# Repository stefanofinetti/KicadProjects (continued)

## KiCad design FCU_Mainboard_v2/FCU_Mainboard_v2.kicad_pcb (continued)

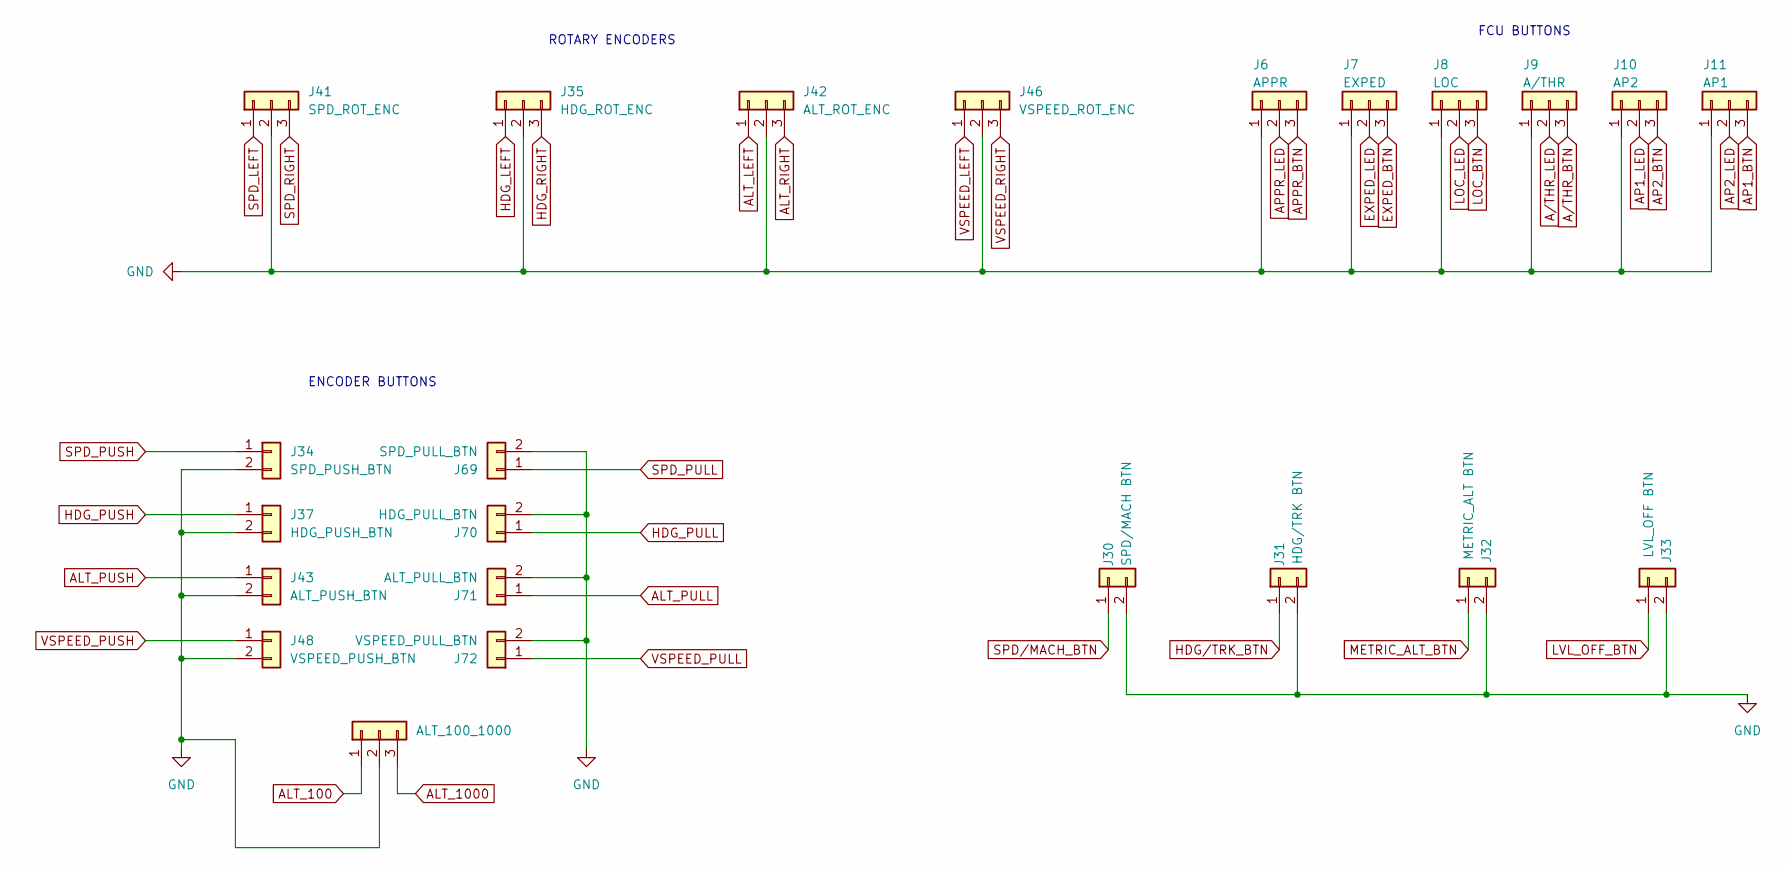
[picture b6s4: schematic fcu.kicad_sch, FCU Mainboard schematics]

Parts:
J6: APPR; JST_EH_B3B-EH-A_1x03_P2.50mm_Vertical
J7: EXPED; JST_EH_B3B-EH-A_1x03_P2.50mm_Vertical
J8: LOC; JST_EH_B3B-EH-A_1x03_P2.50mm_Vertical
J9: A/THR; JST_EH_B3B-EH-A_1x03_P2.50mm_Vertical
J10: AP2; JST_EH_B3B-EH-A_1x03_P2.50mm_Vertical
J11: AP1; JST_EH_B3B-EH-A_1x03_P2.50mm_Vertical
J30: SPD/MACH BTN; JST_EH_B2B-EH-A_1x02_P2.50mm_Vertical
J31: HDG/TRK BTN; JST_EH_B2B-EH-A_1x02_P2.50mm_Vertical
J32: METRIC_ALT BTN; JST_EH_B2B-EH-A_1x02_P2.50mm_Vertical
J33: LVL_OFF BTN; JST_EH_B2B-EH-A_1x02_P2.50mm_Vertical
J34: SPD_PUSH_BTN; JST_EH_B2B-EH-A_1x02_P2.50mm_Vertical
J35: HDG_ROT_ENC; JST_EH_B3B-EH-A_1x03_P2.50mm_Vertical
J37: HDG_PUSH_BTN; JST_EH_B2B-EH-A_1x02_P2.50mm_Vertical
J41: SPD_ROT_ENC; JST_EH_B3B-EH-A_1x03_P2.50mm_Vertical
J42: ALT_ROT_ENC; JST_EH_B3B-EH-A_1x03_P2.50mm_Vertical
J43: ALT_PUSH_BTN; JST_EH_B2B-EH-A_1x02_P2.50mm_Vertical
J45: ALT_100_1000; JST_EH_B3B-EH-A_1x03_P2.50mm_Vertical
J46: VSPEED_ROT_ENC; JST_EH_B3B-EH-A_1x03_P2.50mm_Vertical
J48: VSPEED_PUSH_BTN; JST_EH_B2B-EH-A_1x02_P2.50mm_Vertical
J69: SPD_PULL_BTN; JST_EH_B2B-EH-A_1x02_P2.50mm_Vertical
J70: HDG_PULL_BTN; JST_EH_B2B-EH-A_1x02_P2.50mm_Vertical
J71: ALT_PULL_BTN; JST_EH_B2B-EH-A_1x02_P2.50mm_Vertical
J72: VSPEED_PULL_BTN; JST_EH_B2B-EH-A_1x02_P2.50mm_Vertical

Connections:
ALT_100: J45.1; also elsewhere on the board
ALT_1000: J45.3; also elsewhere on the board
ALT_LEFT: J42.1; also elsewhere on the board
ALT_PULL: J71.1; also elsewhere on the board
ALT_PUSH: J43.1; also elsewhere on the board
ALT_RIGHT: J42.3; also elsewhere on the board
AP1_BTN: J11.3; also elsewhere on the board
AP1_LED: J10.2; also elsewhere on the board
AP2_BTN: J10.3; also elsewhere on the board
AP2_LED: J11.2; also elsewhere on the board
APPR_BTN: J6.3; also elsewhere on the board
APPR_LED: J6.2; also elsewhere on the board
A/THR_BTN: J9.3; also elsewhere on the board
A/THR_LED: J9.2; also elsewhere on the board
EXPED_BTN: J7.3; also elsewhere on the board
EXPED_LED: J7.2; also elsewhere on the board
GND: J6.1, J7.1, J8.1, J9.1, J10.1, J11.1, J30.2, J31.2, J32.2, J33.2, J34.2, J35.2, J37.2, J41.2, J42.2, J43.2, J45.2, J46.2, J48.2, J69.2, J70.2, J71.2, J72.2; also elsewhere on the board
HDG_LEFT: J35.1; also elsewhere on the board
HDG_PULL: J70.1; also elsewhere on the board
HDG_PUSH: J37.1; also elsewhere on the board
HDG_RIGHT: J35.3; also elsewhere on the board
HDG/TRK_BTN: J31.1; also elsewhere on the board
LOC_BTN: J8.3; also elsewhere on the board
LOC_LED: J8.2; also elsewhere on the board
LVL_OFF_BTN: J33.1; also elsewhere on the board
METRIC_ALT_BTN: J32.1; also elsewhere on the board
SPD_LEFT: J41.1; also elsewhere on the board
SPD_PULL: J69.1; also elsewhere on the board
SPD_PUSH: J34.1; also elsewhere on the board
SPD_RIGHT: J41.3; also elsewhere on the board
SPD/MACH_BTN: J30.1; also elsewhere on the board
VSPEED_LEFT: J46.1; also elsewhere on the board
VSPEED_PULL: J72.1; also elsewhere on the board
VSPEED_PUSH: J48.1; also elsewhere on the board
VSPEED_RIGHT: J46.3; also elsewhere on the board

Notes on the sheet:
ROTARY ENCODERS
ENCODER BUTTONS
FCU BUTTONS

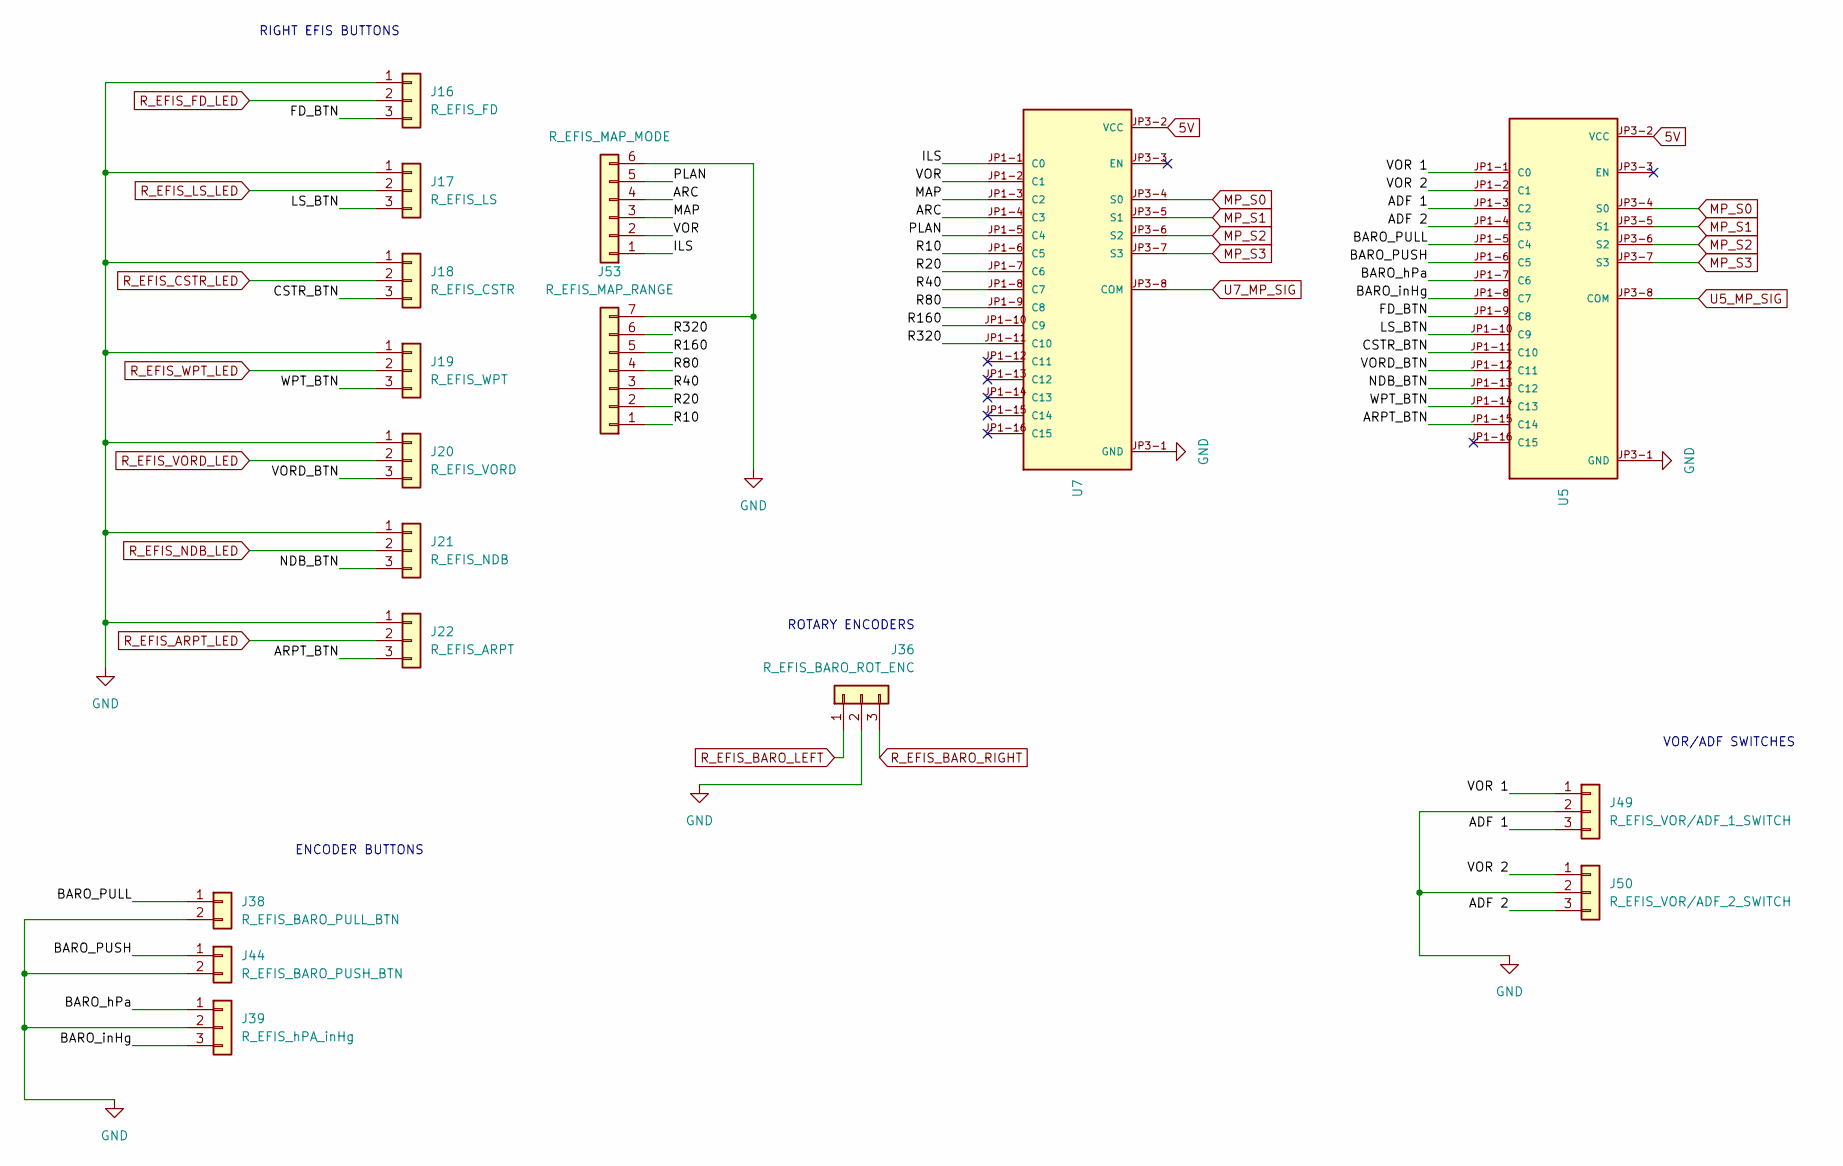
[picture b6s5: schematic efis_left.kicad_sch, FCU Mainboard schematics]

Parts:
J16: R_EFIS_FD; JST_EH_B3B-EH-A_1x03_P2.50mm_Vertical
J17: R_EFIS_LS; JST_EH_B3B-EH-A_1x03_P2.50mm_Vertical
J18: R_EFIS_CSTR; JST_EH_B3B-EH-A_1x03_P2.50mm_Vertical
J19: R_EFIS_WPT; JST_EH_B3B-EH-A_1x03_P2.50mm_Vertical
J20: R_EFIS_VORD; JST_EH_B3B-EH-A_1x03_P2.50mm_Vertical
J21: R_EFIS_NDB; JST_EH_B3B-EH-A_1x03_P2.50mm_Vertical
J22: R_EFIS_ARPT; JST_EH_B3B-EH-A_1x03_P2.50mm_Vertical
J36: R_EFIS_BARO_ROT_ENC; JST_EH_B3B-EH-A_1x03_P2.50mm_Vertical
J38: R_EFIS_BARO_PULL_BTN; JST_EH_B2B-EH-A_1x02_P2.50mm_Vertical
J39: R_EFIS_hPA_inHg; JST_EH_B3B-EH-A_1x03_P2.50mm_Vertical
J44: R_EFIS_BARO_PUSH_BTN; JST_EH_B2B-EH-A_1x02_P2.50mm_Vertical
J49: R_EFIS_VOR/ADF_1_SWITCH; JST_EH_B3B-EH-A_1x03_P2.50mm_Vertical
J50: R_EFIS_VOR/ADF_2_SWITCH; JST_EH_B3B-EH-A_1x03_P2.50mm_Vertical
J51: R_EFIS_MAP_MODE; JST_EH_B6B-EH-A_1x06_P2.50mm_Vertical
J53: R_EFIS_MAP_RANGE; JST_EH_B7B-EH-A_1x07_P2.50mm_Vertical
U5, U7: Multiplexer CD74HC4067 Breakout; MODULE_BOB-09056; PARTREV v11

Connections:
5V: U5.JP3-2 (VCC), U7.JP3-2 (VCC); also elsewhere on the board
/EFIS_LEFT/ADF 1: J49.3, U5.JP1-3 (C2)
/EFIS_LEFT/ADF 2: J50.3, U5.JP1-4 (C3)
/EFIS_LEFT/ARC: J51.4, U7.JP1-4 (C3)
/EFIS_LEFT/ARPT_BTN: J22.3, U5.JP1-15 (C14)
/EFIS_LEFT/BARO_PULL: J38.1, U5.JP1-5 (C4)
/EFIS_LEFT/BARO_PUSH: J44.1, U5.JP1-6 (C5)
/EFIS_LEFT/BARO_hPa: J39.1, U5.JP1-7 (C6)
/EFIS_LEFT/BARO_inHg: J39.3, U5.JP1-8 (C7)
/EFIS_LEFT/CSTR_BTN: J18.3, U5.JP1-11 (C10)
/EFIS_LEFT/FD_BTN: J16.3, U5.JP1-9 (C8)
/EFIS_LEFT/ILS: J51.1, U7.JP1-1 (C0)
/EFIS_LEFT/LS_BTN: J17.3, U5.JP1-10 (C9)
/EFIS_LEFT/MAP: J51.3, U7.JP1-3 (C2)
/EFIS_LEFT/NDB_BTN: J21.3, U5.JP1-13 (C12)
/EFIS_LEFT/PLAN: J51.5, U7.JP1-5 (C4)
/EFIS_LEFT/R10: J53.1, U7.JP1-6 (C5)
/EFIS_LEFT/R20: J53.2, U7.JP1-7 (C6)
/EFIS_LEFT/R40: J53.3, U7.JP1-8 (C7)
/EFIS_LEFT/R80: J53.4, U7.JP1-9 (C8)
/EFIS_LEFT/R160: J53.5, U7.JP1-10 (C9)
/EFIS_LEFT/R320: J53.6, U7.JP1-11 (C10)
/EFIS_LEFT/VOR: J51.2, U7.JP1-2 (C1)
/EFIS_LEFT/VOR 1: J49.1, U5.JP1-1 (C0)
/EFIS_LEFT/VOR 2: J50.1, U5.JP1-2 (C1)
/EFIS_LEFT/VORD_BTN: J20.3, U5.JP1-12 (C11)
/EFIS_LEFT/WPT_BTN: J19.3, U5.JP1-14 (C13)
GND: J16.1, J17.1, J18.1, J19.1, J20.1, J21.1, J22.1, J36.2, J38.2, J39.2, J44.2, J49.2, J50.2, J51.6, J53.7, U5.JP3-1 (GND), U7.JP3-1 (GND); also elsewhere on the board
MP_S0: U5.JP3-4 (S0), U7.JP3-4 (S0); also elsewhere on the board
MP_S1: U5.JP3-5 (S1), U7.JP3-5 (S1); also elsewhere on the board
MP_S2: U5.JP3-6 (S2), U7.JP3-6 (S2); also elsewhere on the board
MP_S3: U5.JP3-7 (S3), U7.JP3-7 (S3); also elsewhere on the board
R_EFIS_ARPT_LED: J22.2; also elsewhere on the board
R_EFIS_BARO_LEFT: J36.1; also elsewhere on the board
R_EFIS_BARO_RIGHT: J36.3; also elsewhere on the board
R_EFIS_CSTR_LED: J18.2; also elsewhere on the board
R_EFIS_FD_LED: J16.2; also elsewhere on the board
R_EFIS_LS_LED: J17.2; also elsewhere on the board
R_EFIS_NDB_LED: J21.2; also elsewhere on the board
R_EFIS_VORD_LED: J20.2; also elsewhere on the board
R_EFIS_WPT_LED: J19.2; also elsewhere on the board
U5_MP_SIG: U5.JP3-8 (COM); also elsewhere on the board
U7_MP_SIG: U7.JP3-8 (COM); also elsewhere on the board

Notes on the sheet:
ENCODER BUTTONS
RIGHT EFIS BUTTONS
VOR/ADF SWITCHES
ROTARY ENCODERS

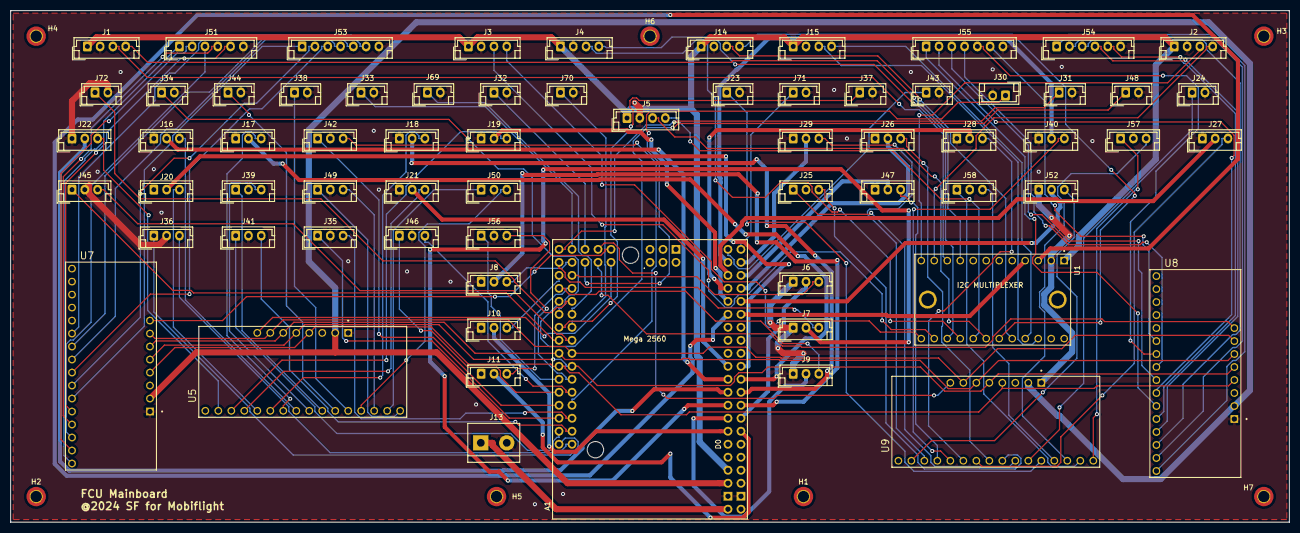
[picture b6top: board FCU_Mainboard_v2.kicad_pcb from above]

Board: 2 copper layers, 250.0 x 100.0 mm, 74 parts (0 on the bottom side), 132 nets.

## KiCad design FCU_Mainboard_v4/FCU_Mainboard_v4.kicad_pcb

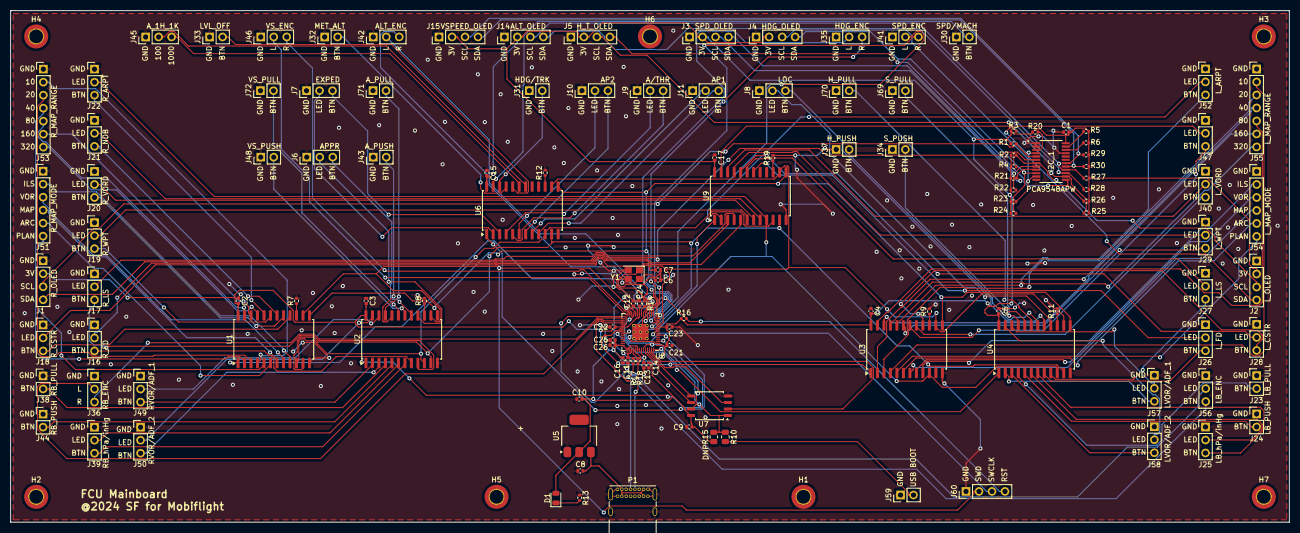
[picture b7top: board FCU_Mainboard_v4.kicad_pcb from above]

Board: 2 copper layers, 250.0 x 100.0 mm, 135 parts (0 on the bottom side), 159 nets.

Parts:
C1, C2, C3, C4, C5, C9, C12, C13, C14, C15, C17, C21, C22, C23, C24, C25, C26: 100nF; Perfect_0402
C6, C7: 15pF; Perfect_0402
C8, C10: 10uF; Perfect_0402
C11, C16: 1uF; Perfect_0402
D1: LED; LED_0805_2012Metric
H1, H2, H3, H4, H5, H6, H7: MountingHole; MountingHole_2.7mm_M2.5_DIN965_Pad_TopBottom
I2C_1: PCA9548APW; SOP65P640X120-24N
J1: R_OLED; PinHeader_1x04_P2.54mm_Vertical
J2: L_OLED; PinHeader_1x04_P2.54mm_Vertical
J3: SPD_OLED; PinHeader_1x04_P2.54mm_Vertical
J4: HDG_OLED; PinHeader_1x04_P2.54mm_Vertical
J5: H_T_OLED; PinHeader_1x04_P2.54mm_Vertical
J6: APPR; PinHeader_1x03_P2.54mm_Vertical
J7: EXPED; PinHeader_1x03_P2.54mm_Vertical
J8: LOC; PinHeader_1x03_P2.54mm_Vertical
J9: A/THR; PinHeader_1x03_P2.54mm_Vertical
J10: AP2; PinHeader_1x03_P2.54mm_Vertical
J11: AP1; PinHeader_1x03_P2.54mm_Vertical
J14: ALT_OLED; PinHeader_1x04_P2.54mm_Vertical
J15: VSPEED_OLED; PinHeader_1x04_P2.54mm_Vertical
J16: R_FD; PinHeader_1x03_P2.54mm_Vertical
J17: R_LS; PinHeader_1x03_P2.54mm_Vertical
J18: R_CSTR; PinHeader_1x03_P2.54mm_Vertical
J19: R_WPT; PinHeader_1x03_P2.54mm_Vertical
J20: R_VORD; PinHeader_1x03_P2.54mm_Vertical
J21: R_NDB; PinHeader_1x03_P2.54mm_Vertical
J22: R_ARPT; PinHeader_1x03_P2.54mm_Vertical
J23: LB_PULL; PinHeader_1x02_P2.54mm_Vertical
J24: LB_PUSH; PinHeader_1x02_P2.54mm_Vertical
J25: LB_hPa/inHg; PinHeader_1x03_P2.54mm_Vertical
J26: L_FD; PinHeader_1x03_P2.54mm_Vertical
J27: L_LS; PinHeader_1x03_P2.54mm_Vertical
J28: L_CSTR; PinHeader_1x03_P2.54mm_Vertical
J29: L_WPT; PinHeader_1x03_P2.54mm_Vertical
J30: SPD/MACH; PinHeader_1x02_P2.54mm_Vertical
J31: HDG/TRK; PinHeader_1x02_P2.54mm_Vertical
J32: MET_ALT; PinHeader_1x02_P2.54mm_Vertical
J33: LVL_OFF; PinHeader_1x02_P2.54mm_Vertical
J34: S_PUSH; PinHeader_1x02_P2.54mm_Vertical
J35: HDG_ENC; PinHeader_1x03_P2.54mm_Vertical
J36: RB_ENC; PinHeader_1x03_P2.54mm_Vertical
J37: H_PUSH; PinHeader_1x02_P2.54mm_Vertical
J38: RB_PULL; PinHeader_1x02_P2.54mm_Vertical
J39: RB_hPa/inHg; PinHeader_1x03_P2.54mm_Vertical
J40: L_VORD; PinHeader_1x03_P2.54mm_Vertical
J41: SPD_ENC; PinHeader_1x03_P2.54mm_Vertical
J42: ALT_ENC; PinHeader_1x03_P2.54mm_Vertical
J43: A_PUSH; PinHeader_1x02_P2.54mm_Vertical
J44: RB_PUSH; PinHeader_1x02_P2.54mm_Vertical
J45: A_1H_1K; PinHeader_1x03_P2.54mm_Vertical
J46: VS_ENC; PinHeader_1x03_P2.54mm_Vertical
J47: L_NDB; PinHeader_1x03_P2.54mm_Vertical
J48: VS_PUSH; PinHeader_1x02_P2.54mm_Vertical
J49: RVOR/ADF_1; PinHeader_1x03_P2.54mm_Vertical
J50: RVOR/ADF_2; PinHeader_1x03_P2.54mm_Vertical
J51: R_MAP_MODE; PinHeader_1x06_P2.54mm_Vertical
J52: L_ARPT; PinHeader_1x03_P2.54mm_Vertical
J53: R_MAP_RANGE; PinHeader_1x07_P2.54mm_Vertical
J54: L_MAP_MODE; PinHeader_1x06_P2.54mm_Vertical
J55: L_MAP_RANGE; PinHeader_1x07_P2.54mm_Vertical
J56: LB_ENC; PinHeader_1x03_P2.54mm_Vertical
J57: LVOR/ADF_1; PinHeader_1x03_P2.54mm_Vertical
J58: LVOR/ADF_2; PinHeader_1x03_P2.54mm_Vertical
J59: Conn_01x02; PinHeader_1x02_P2.54mm_Vertical
J60: RP2040_SWD; PinHeader_1x04_P2.54mm_Vertical
J69: S_PULL; PinHeader_1x02_P2.54mm_Vertical
J70: H_PULL; PinHeader_1x02_P2.54mm_Vertical
J71: A_PULL; PinHeader_1x02_P2.54mm_Vertical
J72: VS_PULL; PinHeader_1x02_P2.54mm_Vertical
P1: USB_C_Plug_USB2.0; USB_C_Receptacle_GCT_USB4085
R1, R2, R3, R4, R5, R6, R21, R22, R23, R24, R25, R26, R27, R28, R29, R30: R4.7K; R_0402_1005Metric
R7, R8, R9, R11, R12, R19, R20: R10K; R_0402_1005Metric
R10: 1k; R_0805_2012Metric
R13: R220; R_0402_1005Metric
R14: 1k; R_0402_1005Metric
R15: DNP; R_0805_2012Metric
R16: 10k; R_0402_1005Metric
R17, R18: 27.4; R_0402_1005Metric
U1, U2, U3, U4, U6, U9: CD74HC4067M; SOIC-24W_7.5x15.4mm_P1.27mm
U5: NCP1117-3.3_SOT223; SOT-223
U7: W25Q128JVS; SOIC-8_5.23x5.23mm_P1.27mm
U8: RP2040; QFN-56-1EP_7x7mm_P0.4mm_EP3.2x3.2mm
Y1: X322512MSB4SI; Crystal_SMD_3225-4Pin_3.2x2.5mm

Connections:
+1V1: C11.1, C12.1, C13.1, U8.23 (DVDD), U8.45 (VREG_VOUT), U8.50 (DVDD)
+3V3: C1.1, C2.1, C3.1, C4.1, C5.1, C9.1, C10.1, C14.1, C15.1, C16.1, C17.1, C21.1, C22.1, C23.1, C24.1, C25.1, C26.1, D1.2 (A), I2C_1.24 (VCC), J1.2, J2.2, J3.2, J4.2, J5.2, J14.2, J15.2, R1.1, R2.2, R3.1, R4.1, R5.2, R6.1, R15.1, R16.1, R20.1, R21.1, R22.1, R23.1, R24.1, R25.1, R26.1, R27.1, R28.1, R29.1, R30.1, U1.24 (VCC), U2.24 (VCC), U3.24 (VCC), U4.24 (VCC), U5.2 (VO), U6.24 (VCC), U7.8 (VCC), U8.1 (IOVDD), U8.10 (IOVDD), U8.22 (IOVDD), U8.33 (IOVDD), U8.42 (IOVDD), U8.43 (ADC_AVDD), U8.44 (VREG_IN), U8.48 (USB_VDD), U8.49 (IOVDD), U9.24 (VCC)
+5V: C8.1, P1.A4 (VBUS), P1.A9 (VBUS), P1.B4 (VBUS), P1.B9 (VBUS), U5.3 (VI)
/OLEDs/ALT_SCL: I2C_1.16 (SC5), J14.3, R27.2
/OLEDs/ALT_SDA: I2C_1.15 (SD5), J14.4, R28.2
/OLEDs/HDG_SCL: I2C_1.11 (SC3), J4.3, R23.2
/OLEDs/HDG_SDA: I2C_1.10 (SD3), J4.4, R24.2
/OLEDs/HDG/TRK_SCL: I2C_1.14 (SC4), J5.3, R25.2
/OLEDs/HDG/TRK_SDA: I2C_1.13 (SD4), J5.4, R26.2
/OLEDs/L_EFIS_SCL: I2C_1.7 (SC1), J2.3, R1.2
/OLEDs/L_EFIS_SDA: I2C_1.4 (SD0), J2.4, R3.2
/OLEDs/R_EFIS_SCL: I2C_1.5 (SC0), J1.3, R2.1
/OLEDs/R_EFIS_SDA: I2C_1.6 (SD1), J1.4, R4.2
/OLEDs/SPD_SCL: I2C_1.9 (SC2), J3.3, R21.2
/OLEDs/SPD_SDA: I2C_1.8 (SD2), J3.4, R22.2
/OLEDs/VSPEED_SCL: I2C_1.18 (SC6), J15.3, R29.2
/OLEDs/VSPEED_SDA: I2C_1.17 (SD6), J15.4, R30.2
/QSPI_SCLK: U7.6 (CLK), U8.52 (QSPI_SCLK)
/QSPI_SD0: U7.5 (DI(IO0)), U8.53 (QSPI_SD0)
/QSPI_SD1: U7.2 (DO(IO1)), U8.55 (QSPI_SD1)
/QSPI_SD2: U7.3 (IO2), U8.54 (QSPI_SD2)
/QSPI_SD3: U7.7 (IO3), U8.51 (QSPI_SD3)
/QSPI_SS: R10.1, R15.2, U7.1 (~CS), U8.56 (QSPI_SS)
/SWCLK: J60.3, U8.25 (SWD)
/SWD: J60.2, U8.24 (SWCLK)
/USB_D+: P1.A6 (D+), R17.1
/USB_D-: P1.A7 (D-), R18.1
/XIN: C6.1, U8.20 (XIN), Y1.3
/XOUT: R14.1, U8.21 (XOUT)
/~RST: J60.4, R16.2, U8.26 (RUN)
/~USB_BOOT: J59.2, R10.2
ALT_100: J45.2, U6.18 (I13)
ALT_1000: J45.3, U6.19 (I12)
ALT_LEFT: J42.2, U8.18 (GPIO15)
ALT_PULL: J71.2, U2.21 (I10)
ALT_PUSH: J43.2, U2.20 (I11)
ALT_RIGHT: J42.3, U8.17 (GPIO14)
AP1_BTN: J11.3, U6.9 (I0)
AP1_LED: J11.2, U6.8 (I1)
AP2_BTN: J10.3, U6.7 (I2)
AP2_LED: J10.2, U6.6 (I3)
APPR_BTN: J6.3, U2.17 (I14)
APPR_LED: J6.2, U2.16 (I15)
A/THR_BTN: J9.3, U6.5 (I4)
A/THR_LED: J9.2, U6.4 (I5)
EXPED_BTN: J7.3, U6.3 (I6)
EXPED_LED: J7.2, U6.2 (I7)
GND: C1.2, C2.2, C3.2, C4.2, C5.2, C6.2, C7.2, C8.2, C9.2, C10.2, C11.2, C12.2, C13.2, C14.2, C15.2, C16.2, C17.2, C21.2, C22.2, C23.2, C24.2, C25.2, C26.2, I2C_1.1 (A0), I2C_1.2 (A1), I2C_1.12 (GND), I2C_1.21 (A2), J1.1, J2.1, J3.1, J4.1, J5.1, J6.1, J7.1, J8.1, J9.1, J10.1, J11.1, J14.1, J15.1, J16.1, J17.1, J18.1, J19.1, J20.1, J21.1, J22.1, J23.1, J24.1, J25.1, J26.1, J27.1, J28.1, J29.1, J30.1, J31.1, J32.1, J33.1, J34.1, J35.1, J36.1, J37.1, J38.1, J39.1, J40.1, J41.1, J42.1, J43.1, J44.1, J45.1, J46.1, J47.1, J48.1, J49.1, J50.1, J51.1, J52.1, J53.1, J54.1, J55.1, J56.1, J57.1, J58.1, J59.1, J60.1, J69.1, J70.1, J71.1, J72.1, P1.A1 (GND), P1.A12 (GND), P1.B1 (GND), P1.B12 (GND), P1.S1 (SHIELD), R7.2, R8.2, R9.2, R11.2, R12.2, R13.1, R19.2, U1.12 (GND), U2.12 (GND), U3.12 (GND), U4.12 (GND), U5.1 (GND), U6.12 (GND), U7.4 (GND), U8.19 (TESTEN), U8.57 (GND), U9.12 (GND), Y1.2, Y1.4
HDG_LEFT: J35.2, U8.16 (GPIO13)
HDG_PULL: J70.2, U4.19 (I12)
HDG_PUSH: J37.2, U4.18 (I13)
HDG_RIGHT: J35.3, U8.15 (GPIO12)
HDG/TRK_BTN: J31.2, U6.22 (I9)
LOC_BTN: J8.3, U4.17 (I14)
LOC_LED: J8.2, U4.16 (I15)
LVL_OFF_BTN: J33.2, U6.20 (I11)
L_ADF_1: J57.3, U4.2 (I7)
L_ADF_2: J58.3, U4.3 (I6)
L_ARC: J54.5, U3.6 (I3)
L_ARPT_BTN: J52.3, U3.20 (I11)
L_BARO_PULL: J23.2, U4.4 (I5)
L_BARO_PUSH: J24.2, U4.5 (I4)
L_BARO_hPa: J25.2, U4.6 (I3)
L_BARO_inHg: J25.3, U4.7 (I2)
L_CSTR_BTN: J28.3, U3.16 (I15)
L_EFIS_ARPT_LED: J52.2, U9.2 (I7)
L_EFIS_BARO_LEFT: J56.2, U8.32 (GPIO21)
L_EFIS_BARO_RIGHT: J56.3, U8.31 (GPIO20)
L_EFIS_CSTR_LED: J28.2, U9.20 (I11)
L_EFIS_FD_LED: J26.2, U9.18 (I13)
L_EFIS_LS_LED: J27.2, U9.19 (I12)
L_EFIS_NDB_LED: J47.2, U9.23 (I8)
L_EFIS_VORD_LED: J40.2, U9.22 (I9)
L_EFIS_WPT_LED: J29.2, U9.21 (I10)
L_FD_BTN: J26.3, U4.8 (I1)
L_ILS: J54.2, U3.9 (I0)
L_LS_BTN: J27.3, U4.9 (I0)
L_MAP: J54.4, U3.7 (I2)
L_NDB_BTN: J47.3, U3.18 (I13)
L_PLAN: J54.6, U3.5 (I4)
L_R10: J55.2, U3.4 (I5)
L_R20: J55.3, U3.3 (I6)
L_R40: J55.4, U3.2 (I7)
L_R80: J55.5, U3.23 (I8)
L_R160: J55.6, U3.22 (I9)
L_R320: J55.7, U3.21 (I10)
L_VOR: J54.3, U3.8 (I1)
L_VORD_BTN: J40.3, U3.17 (I14)
L_VOR_1: J57.2, U4.22 (I9)
L_VOR_2: J58.2, U4.23 (I8)
L_WPT_BTN: J29.3, U3.19 (I12)
METRIC_ALT_BTN: J32.2, U6.21 (I10)
MP_S0: U1.10 (S0), U2.10 (S0), U3.10 (S0), U4.10 (S0), U6.10 (S0), U8.8 (GPIO6), U9.10 (S0)
MP_S1: U1.11 (S1), U2.11 (S1), U3.11 (S1), U4.11 (S1), U6.11 (S1), U8.9 (GPIO7), U9.11 (S1)
MP_S2: U1.14 (S2), U2.14 (S2), U3.14 (S2), U4.14 (S2), U6.14 (S2), U8.11 (GPIO8), U9.14 (S2)
MP_S3: U1.13 (S3), U2.13 (S3), U3.13 (S3), U4.13 (S3), U6.13 (S3), U8.12 (GPIO9), U9.13 (S3)
unnamed: C7.1, R14.2, Y1.1
unnamed: D1.1 (K), R13.2
unnamed: I2C_1.3 (~RESET), R20.2
unnamed: R7.1, U1.15 (~E)
unnamed: R8.1, U2.15 (~E)
unnamed: R9.1, U3.15 (~E)
unnamed: R11.1, U4.15 (~E)
unnamed: R12.1, U6.15 (~E)
unnamed: R18.2, U8.46 (USB_DM)
unnamed: R17.2, U8.47 (USB_DP)
unnamed: R19.1, U9.15 (~E)
R_ADF_1: J49.3, U2.2 (I7)
R_ADF_2: J50.3, U2.3 (I6)
R_ARC: J51.5, U1.6 (I3)
R_ARPT_BTN: J22.3, U1.20 (I11)
R_BARO_PULL: J38.2, U2.4 (I5)
R_BARO_PUSH: J44.2, U2.5 (I4)
R_BARO_hPa: J39.2, U2.6 (I3)
R_BARO_inHg: J39.3, U2.7 (I2)
R_CSTR_BTN: J18.3, U1.16 (I15)
R_EFIS_ARPT_LED: J22.2, U9.9 (I0)
R_EFIS_BARO_LEFT: J36.2, U8.30 (GPIO19)
R_EFIS_BARO_RIGHT: J36.3, U8.29 (GPIO18)
R_EFIS_CSTR_LED: J18.2, U9.5 (I4)
R_EFIS_FD_LED: J16.2, U9.3 (I6)
R_EFIS_LS_LED: J17.2, U9.4 (I5)
R_EFIS_NDB_LED: J21.2, U9.8 (I1)
R_EFIS_VORD_LED: J20.2, U9.7 (I2)
R_EFIS_WPT_LED: J19.2, U9.6 (I3)
R_FD_BTN: J16.3, U2.8 (I1)
R_ILS: J51.2, U1.9 (I0)
R_LS_BTN: J17.3, U2.9 (I0)
R_MAP: J51.4, U1.7 (I2)
R_NDB_BTN: J21.3, U1.18 (I13)
R_PLAN: J51.6, U1.5 (I4)
R_R10: J53.2, U1.4 (I5)
R_R20: J53.3, U1.3 (I6)
R_R40: J53.4, U1.2 (I7)
R_R80: J53.5, U1.23 (I8)
R_R160: J53.6, U1.22 (I9)
R_R320: J53.7, U1.21 (I10)
R_VOR: J51.3, U1.8 (I1)
R_VORD_BTN: J20.3, U1.17 (I14)
R_VOR_1: J49.2, U2.22 (I9)
R_VOR_2: J50.2, U2.23 (I8)
R_WPT_BTN: J19.3, U1.19 (I12)
SCL: I2C_1.22 (SCL), R5.1
SDA: I2C_1.23 (SDA), R6.2
SPD_LEFT: J41.2, U8.14 (GPIO11)
SPD_PULL: J69.2, U4.21 (I10)
SPD_PUSH: J34.2, U4.20 (I11)
SPD_RIGHT: J41.3, U8.13 (GPIO10)
SPD/MACH_BTN: J30.2, U6.23 (I8)
U1_MP_SIG: U1.1 (COM), U8.2 (GPIO0)
U2_MP_SIG: U2.1 (COM), U8.3 (GPIO1)
U3_MP_SIG: U3.1 (COM), U8.34 (GPIO22)
U4_MP_SIG: U4.1 (COM), U8.35 (GPIO23)
U5_MP_SIG: U6.1 (COM), U8.6 (GPIO4)
U6_MP_SIG: U8.36 (GPIO24), U9.1 (COM)
VSPEED_LEFT: J46.2, U8.28 (GPIO17)
VSPEED_PULL: J72.2, U2.19 (I12)
VSPEED_PUSH: J48.2, U2.18 (I13)
VSPEED_RIGHT: J46.3, U8.27 (GPIO16)

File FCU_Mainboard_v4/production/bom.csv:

Designator,Footprint,Quantity,Value,LCSC Part #
"C1, C12, C13, C14, C15, C17, C2, C21, C22, C23, C24, C25, C26, C3, C4, C5, C9",Perfect_0402,17,100nF,
"C10, C8",Perfect_0402,2,10uF,
"C11, C16",Perfect_0402,2,1uF,
"C6, C7",Perfect_0402,2,15pF,
D1,0805,1,LED,
"H1, H2, H3, H4, H5, H6, H7",MountingHole_2.7mm_M2.5_DIN965_Pad_TopBottom,7,MountingHole,
I2C_1,SOP65P640X120-24N,1,PCA9548APW,
J1,PinHeader_1x04_P2.54mm_Vertical,1,R_OLED,
J10,PinHeader_1x03_P2.54mm_Vertical,1,AP2,
J11,PinHeader_1x03_P2.54mm_Vertical,1,AP1,
J14,PinHeader_1x04_P2.54mm_Vertical,1,ALT_OLED,
J15,PinHeader_1x04_P2.54mm_Vertical,1,VSPEED_OLED,
J16,PinHeader_1x03_P2.54mm_Vertical,1,R_FD,
J17,PinHeader_1x03_P2.54mm_Vertical,1,R_LS,
J18,PinHeader_1x03_P2.54mm_Vertical,1,R_CSTR,
J19,PinHeader_1x03_P2.54mm_Vertical,1,R_WPT,
J2,PinHeader_1x04_P2.54mm_Vertical,1,L_OLED,
J20,PinHeader_1x03_P2.54mm_Vertical,1,R_VORD,
J21,PinHeader_1x03_P2.54mm_Vertical,1,R_NDB,
J22,PinHeader_1x03_P2.54mm_Vertical,1,R_ARPT,
J23,PinHeader_1x02_P2.54mm_Vertical,1,LB_PULL,
J24,PinHeader_1x02_P2.54mm_Vertical,1,LB_PUSH,
J25,PinHeader_1x03_P2.54mm_Vertical,1,LB_hPa/inHg,
J26,PinHeader_1x03_P2.54mm_Vertical,1,L_FD,
J27,PinHeader_1x03_P2.54mm_Vertical,1,L_LS,
J28,PinHeader_1x03_P2.54mm_Vertical,1,L_CSTR,
J29,PinHeader_1x03_P2.54mm_Vertical,1,L_WPT,
J3,PinHeader_1x04_P2.54mm_Vertical,1,SPD_OLED,
J30,PinHeader_1x02_P2.54mm_Vertical,1,SPD/MACH,
J31,PinHeader_1x02_P2.54mm_Vertical,1,HDG/TRK,
J32,PinHeader_1x02_P2.54mm_Vertical,1,MET_ALT,
J33,PinHeader_1x02_P2.54mm_Vertical,1,LVL_OFF,
J34,PinHeader_1x02_P2.54mm_Vertical,1,S_PUSH,
J35,PinHeader_1x03_P2.54mm_Vertical,1,HDG_ENC,
J36,PinHeader_1x03_P2.54mm_Vertical,1,RB_ENC,
J37,PinHeader_1x02_P2.54mm_Vertical,1,H_PUSH,
J38,PinHeader_1x02_P2.54mm_Vertical,1,RB_PULL,
J39,PinHeader_1x03_P2.54mm_Vertical,1,RB_hPa/inHg,
J4,PinHeader_1x04_P2.54mm_Vertical,1,HDG_OLED,
J40,PinHeader_1x03_P2.54mm_Vertical,1,L_VORD,
J41,PinHeader_1x03_P2.54mm_Vertical,1,SPD_ENC,
J42,PinHeader_1x03_P2.54mm_Vertical,1,ALT_ENC,
J43,PinHeader_1x02_P2.54mm_Vertical,1,A_PUSH,
J44,PinHeader_1x02_P2.54mm_Vertical,1,RB_PUSH,
J45,PinHeader_1x03_P2.54mm_Vertical,1,A_1H_1K,
J46,PinHeader_1x03_P2.54mm_Vertical,1,VS_ENC,
J47,PinHeader_1x03_P2.54mm_Vertical,1,L_NDB,
J48,PinHeader_1x02_P2.54mm_Vertical,1,VS_PUSH,
J49,PinHeader_1x03_P2.54mm_Vertical,1,RVOR/ADF_1,
J5,PinHeader_1x04_P2.54mm_Vertical,1,H_T_OLED,
J50,PinHeader_1x03_P2.54mm_Vertical,1,RVOR/ADF_2,
J51,PinHeader_1x06_P2.54mm_Vertical,1,R_MAP_MODE,
J52,PinHeader_1x03_P2.54mm_Vertical,1,L_ARPT,
J53,PinHeader_1x07_P2.54mm_Vertical,1,R_MAP_RANGE,
J54,PinHeader_1x06_P2.54mm_Vertical,1,L_MAP_MODE,
J55,PinHeader_1x07_P2.54mm_Vertical,1,L_MAP_RANGE,
J56,PinHeader_1x03_P2.54mm_Vertical,1,LB_ENC,
J57,PinHeader_1x03_P2.54mm_Vertical,1,LVOR/ADF_1,
J58,PinHeader_1x03_P2.54mm_Vertical,1,LVOR/ADF_2,
J59,PinHeader_1x02_P2.54mm_Vertical,1,Conn_01x02,
J6,PinHeader_1x03_P2.54mm_Vertical,1,APPR,
J60,PinHeader_1x04_P2.54mm_Vertical,1,RP2040_SWD,
J69,PinHeader_1x02_P2.54mm_Vertical,1,S_PULL,
J7,PinHeader_1x03_P2.54mm_Vertical,1,EXPED,
J70,PinHeader_1x02_P2.54mm_Vertical,1,H_PULL,
J71,PinHeader_1x02_P2.54mm_Vertical,1,A_PULL,
J72,PinHeader_1x02_P2.54mm_Vertical,1,VS_PULL,
J8,PinHeader_1x03_P2.54mm_Vertical,1,LOC,
J9,PinHeader_1x03_P2.54mm_Vertical,1,A/THR,
P1,USB_C_Receptacle_GCT_USB4085,1,USB_C_Plug_USB2.0,
"R1, R2, R21, R22, R23, R24, R25, R26, R27, R28, R29, R3, R30, R4, R5, R6",0402,16,R4.7K,
R10,0805,1,1k,
"R11, R12, R19, R20, R7, R8, R9",0402,7,R10K,
R13,0402,1,R220,
R14,0402,1,1k,
R16,0402,1,10k,
"R17, R18",0402,2,27.4,
"U1, U2, U3, U4, U6, U9",SOIC-24W_7.5x15.4mm_P1.27mm,6,CD74HC4067M,
U5,SOT-223,1,NCP1117-3.3_SOT223,
U7,SOIC-8_5.23x5.23mm_P1.27mm,1,W25Q128JVS,
U8,QFN-56-1EP_7x7mm_P0.4mm_EP3.2x3.2mm,1,RP2040,
Y1,Crystal_SMD_3225-4Pin_3.2x2.5mm,1,X322512MSB4SI,

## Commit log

2024-10-21 Initial commit of my Kicad Projects
2024-10-21 GIT Ignore
2024-10-21 Added Readme.md file
2024-10-21 Amended readme
